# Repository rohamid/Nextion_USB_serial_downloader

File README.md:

# Nextion USB Serial Downloader #
This is `FTDI` based USB serial for downloading Nextion HMI directly using USB without copying the HMI file to SD card and updated later. It also equipped with DC-DC buck converter for supplying LCD without USB. This Tools also allowed to connect to microcontroller and using digital switch.

## Nextion USB Serial Downloader PCB ##

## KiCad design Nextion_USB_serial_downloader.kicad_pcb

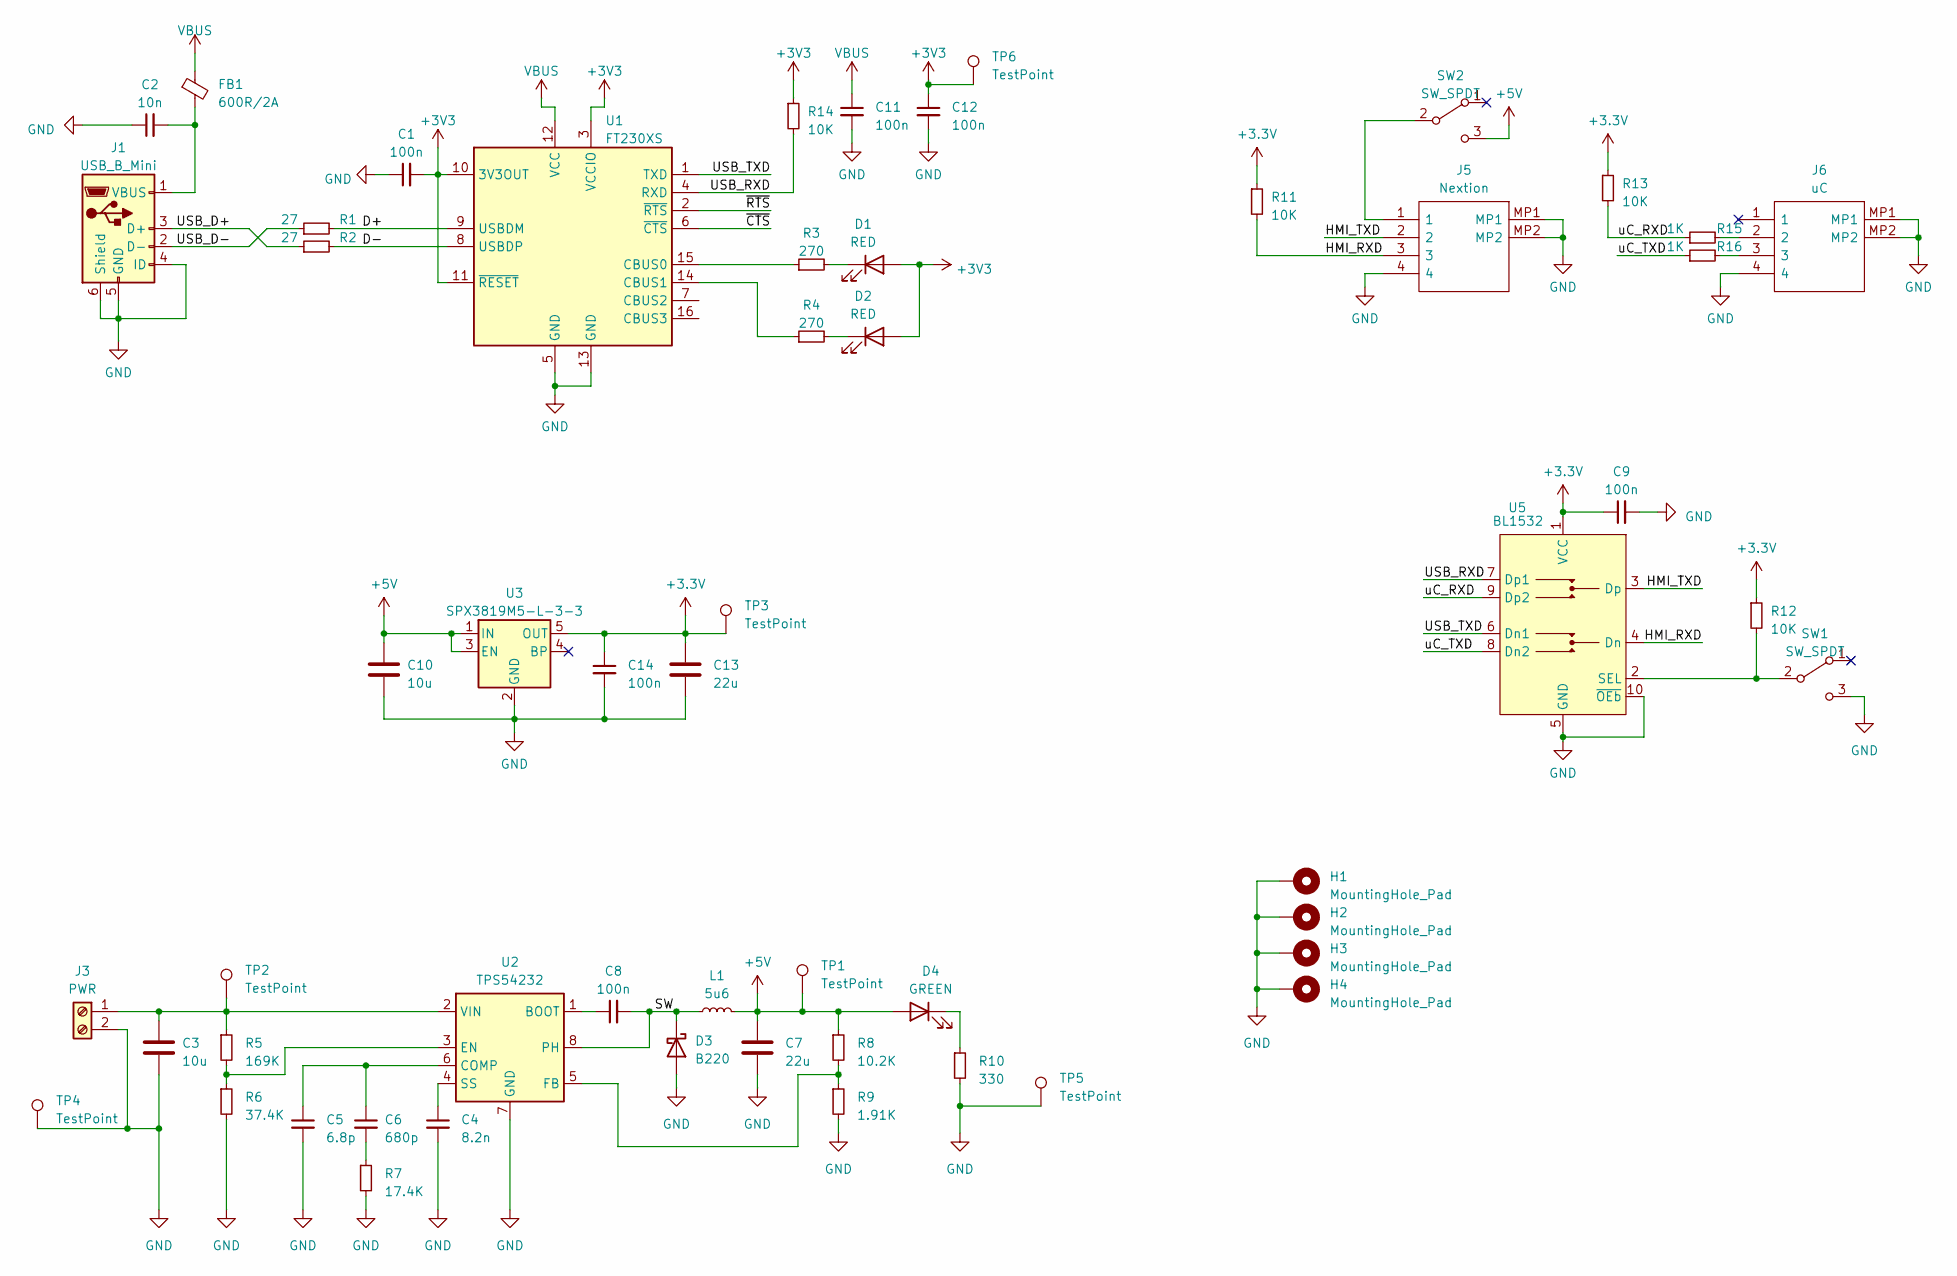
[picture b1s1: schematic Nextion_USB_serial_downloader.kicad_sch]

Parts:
C1, C8, C9, C11, C12, C14: 100n; C_0603_1608Metric; LCSC Part Number C14663
C2: 10n; C_0603_1608Metric; LCSC Part Number C57112
C3, C10: 10u; C_0805_2012Metric; LCSC Part Number C15850
C4: 8.2n; C_0603_1608Metric; LCSC Part Number C1596
C5: 6.8p; C_0603_1608Metric; LCSC Part Number C1679
C6: 680p; C_0603_1608Metric; LCSC Part Number C1630
C7, C13: 22u; C_0805_2012Metric; LCSC Part Number C45783
D1, D2: RED; LED_0805_2012Metric; LCSC Part Number C84256
D3: B220; D_SMA; LCSC Part Number C110481
D4: GREEN; LED_0805_2012Metric; LCSC Part Number C2297
FB1: 600R/2A; L_0805_2012Metric; LCSC Part Number C1017
H1, H2, H3, H4: MountingHole_Pad; MountingHole_3.2mm_M3_Pad_Via
J1: USB_B_Mini; USB_Mini-B_Lumberg_2486_01_Horizontal; LCSC Part Number C508689
J3: PWR; TerminalBlock_bornier-2_P5.08mm
J5: Nextion; S4BXHSM4TBLFSN; Manufacturer_Part_Number S4B-XH-SM4-TB(LF)(SN); LCSC Part Number C2764243
J6: uC; S4BXHSM4TBLFSN; Manufacturer_Part_Number S4B-XH-SM4-TB(LF)(SN); LCSC Part Number C2764243
L1: 5u6; L_Sunlord_MWSA0603S; LCSC Part Number C408448
R1, R2: 27; R_0603_1608Metric; LCSC Part Number C25190
R3, R4: 270; R_0603_1608Metric; LCSC Part Number C22966
R5: 169K; R_0603_1608Metric; LCSC Part Number C403021
R6: 37.4K; R_0603_1608Metric; LCSC Part Number C137814
R7: 17.4K; R_0603_1608Metric; LCSC Part Number C227623
R8: 10.2K; R_0603_1608Metric; LCSC Part Number C706118
R9: 1.91K; R_0603_1608Metric; LCSC Part Number C217858
R10: 330; R_0603_1608Metric; LCSC Part Number C23138
R11, R12, R13, R14: 10K; R_0603_1608Metric; LCSC Part Number C25804
R15, R16: 1K; R_0603_1608Metric; LCSC Part Number C21190
SW1, SW2: SW_SPDT; SW_CuK_OS102011MA1QN1_SPDT_Angled
TP1, TP2, TP3, TP4, TP5, TP6: TestPoint; TestPoint_Pad_D1.5mm
U1: FT230XS; SSOP-16_3.9x4.9mm_P0.635mm; LCSC Part Number C69082
U2: TPS54232; SOIC-8_3.9x4.9mm_P1.27mm; LCSC Part Number C52653
U3: SPX3819M5-L-3-3; SOT-23-5; LCSC Part Number C9055
U5: BL1532; MSOP-10_3x3mm_P0.5mm; LCSC Part Number C248370

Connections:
+3.3V: C9.1, C13.1, C14.1, R11.1, R12.1, R13.1, TP3.1, U3.5 (OUT), U5.1 (VCC)
+3V3: C1.2, C12.1, D1.2 (A), D2.2 (A), R14.1, TP6.1, U1.3 (VCCIO), U1.10 (3V3OUT), U1.11 (~RESET)
+5V: C7.1, C10.1, D4.2 (A), L1.2, R8.1, SW2.3 (C), TP1.1, U3.1 (IN), U3.3 (EN)
/D+: R1.2, U1.9 (USBDM)
/D-: R2.2, U1.8 (USBDP)
/HMI_RXD: J5.3, R11.2, U5.4 (Dn)
/HMI_TXD: J5.2, U5.3 (Dp)
/SW: C8.2, D3.1 (K), L1.1, U2.8 (PH)
/USB_D+: J1.3 (D+), R2.1
/USB_D-: J1.2 (D-), R1.1
/USB_RXD: R14.2, U1.4 (RXD), U5.7 (Dp1)
/USB_TXD: U1.1 (TXD), U5.6 (Dn1)
/uC_RXD: R13.2, R15.1, U5.9 (Dp2)
/uC_TXD: R16.1, U5.8 (Dn2)
/~CTS: U1.6 (~CTS)
/~RTS: U1.2 (~RTS)
GND: C1.1, C2.1, C3.2, C4.2, C5.2, C7.2, C9.2, C10.2, C11.2, C12.2, C13.2, C14.2, D3.2 (A), H1.1, H2.1, H3.1, H4.1, J1.4 (ID), J1.5 (GND), J1.6 (Shield), J3.2, J5.4, J5.MP1, J5.MP2, J6.4, J6.MP1, J6.MP2, R6.2, R7.2, R9.2, R10.2, SW1.3 (C), TP4.1, TP5.1, U1.5 (GND), U1.13 (GND), U2.7 (GND), U3.2 (GND), U5.5 (GND), U5.10 (~OEb)
unnamed: C6.2, R7.1
unnamed: D1.1 (K), R3.2
unnamed: D2.1 (K), R4.2
unnamed: D4.1 (K), R10.1
unnamed: C2.2, FB1.2, J1.1 (VBUS)
unnamed: C3.1, J3.1, R5.1, TP2.1, U2.2 (VIN)
unnamed: J6.2, R15.2
unnamed: J6.3, R16.2
unnamed: R12.2, SW1.2 (B), U5.2 (SEL)
unnamed: J5.1, SW2.2 (B)
unnamed: R3.1, U1.15 (CBUS0)
unnamed: R4.1, U1.14 (CBUS1)
unnamed: C8.1, U2.1 (BOOT)
unnamed: C5.1, C6.1, U2.6 (COMP)
unnamed: R5.2, R6.1, U2.3 (EN)
unnamed: R8.2, R9.1, U2.5 (FB)
unnamed: C4.1, U2.4 (SS)
VBUS: C11.1, FB1.1, U1.12 (VCC)

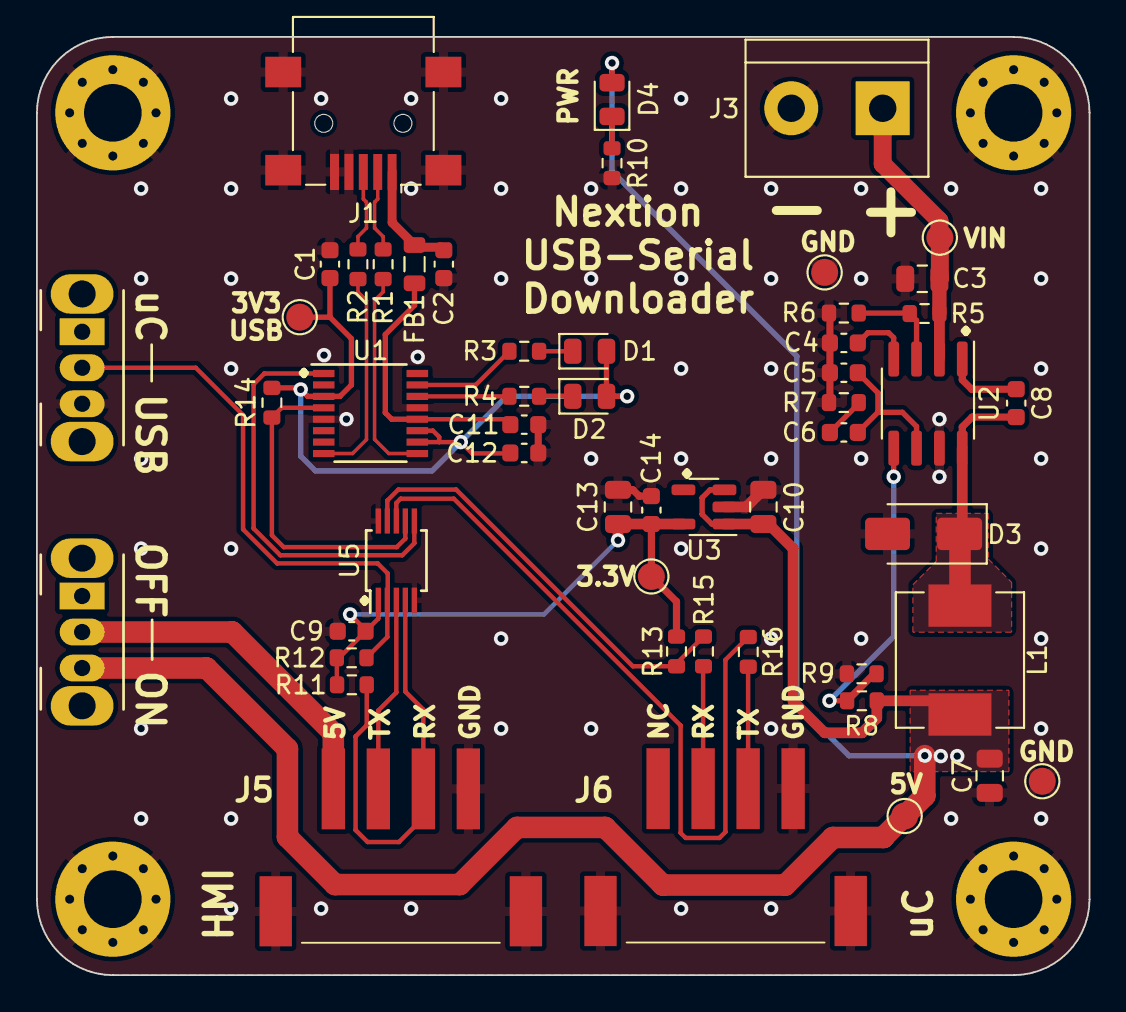
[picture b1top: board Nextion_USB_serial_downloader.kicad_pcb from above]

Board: 2 copper layers, 58.5 x 52.1 mm, 56 parts (0 on the bottom side), 33 nets.
